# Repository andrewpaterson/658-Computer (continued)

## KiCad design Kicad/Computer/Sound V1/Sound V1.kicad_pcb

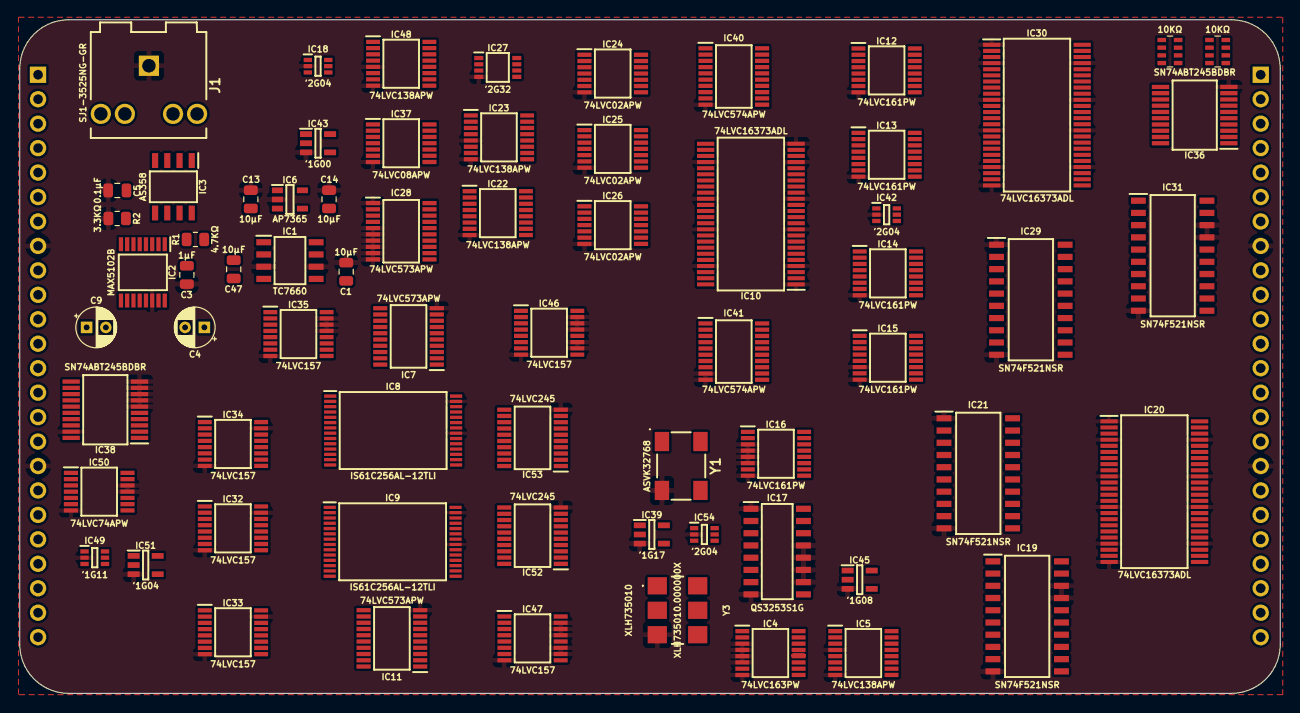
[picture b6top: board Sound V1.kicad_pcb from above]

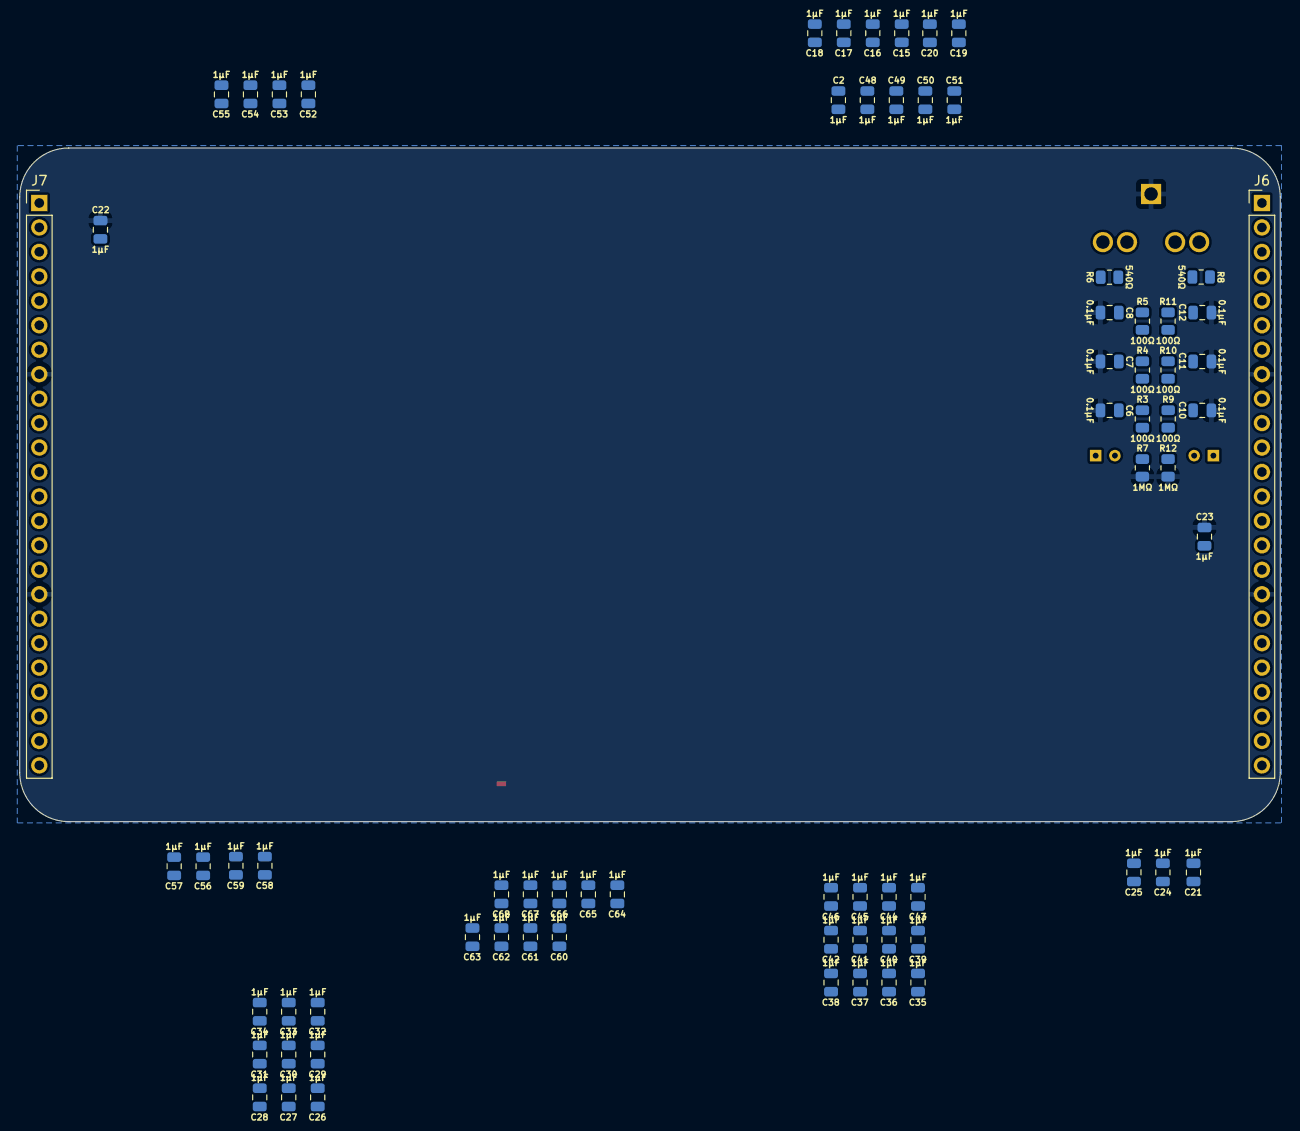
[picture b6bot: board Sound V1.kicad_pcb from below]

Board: 2 copper layers, 130.9 x 70.0 mm, 141 parts (72 on the bottom side), 233 nets, no tracks yet.

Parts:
C1, C13, C14, C47: 10µF; C_0805
C2, C3, C15, C16, C17, C18, C19, C20, C21, C22, C23, C24, C25, C26, C27, C28, C29, C30, C31, C32, C33, C34, C35, C36, C37, C38, C39, C40, C41, C42, C43, C44, C45, C46, C48, C49, C50, C51, C52, C53, C54, C55, C56, C57, C58, C59, C60, C61, C62, C63, C64, C65, C66, C67, C68: 1μF; C_0805
C4, C9: C_Polarized; CP_Radial_D4.0mm_P2.00mm
C5, C6, C7, C8, C10, C11, C12: 0.1μF; C_0805
IC1: TC7660EOA; SOIC127P600X175-8N
IC2: MAX5102BEUE+T; SOP65P640X110-16N
IC3: AS358AMTR-G1; SOIC127P600X175-8N
IC4: 74LVC163PW,118; SOP65P640X110-16N
IC5, IC22, IC23, IC48: 74LVC138APW-Q100J; SOP65P640X110-16N
IC6: AP7365-33WG-7; SOT95P285X130-5N
IC7, IC11, IC28: 74LVC573APW,118; SOP65P640X110-20N
IC8, IC9: IS61C256AL-12TLI; SOP55P1340X120-28N
IC10, IC20, IC30: 74LVC16373ADL,118; SOP64P1025X280-48N
IC12, IC13, IC14, IC15, IC16: 74LVC161PW,112; SOP65P640X110-16N
IC17: QS3253S1G; SOIC127P602X173-16N
IC18, IC42, IC54: 74LVC2G04GW-Q100H; SOP65P210X110-6N
IC19, IC21, IC29, IC31: SN74F521NSR; SOIC127P780X200-20N
IC24, IC25, IC26: 74LVC02APW,118; SOP65P640X110-14N
IC27: 74LVC2G32DP,125; SOP65P400X110-8N
IC32, IC33, IC34, IC35, IC46, IC47: 74LVC157APW,118; SOP65P640X110-16N
IC36, IC38: SN74ABT245BDBR; SOP65P780X200-20N
IC37: 74LVC08APW,112; SOP65P640X110-14N
IC39: 74LVC1G17GV,125; SOT95P275X110-5N
IC40, IC41: 74LVC574APW,118; SOP65P640X110-20N
IC43: 74LVC1G00GV,125; SOT95P275X110-5N
IC45: 74LVC1G08GV,125; SOT95P275X110-5N
IC49: 74LVC1G11GW-Q100H; SOP65P210X110-6N
IC50: 74LVC74APW,118; SOP65P640X110-14N
IC51: 74LVC1G04GV,125; SOT95P275X110-5N
IC52, IC53: 74LVC245AT20; SOP65P640X120-20N
J1: SJ1-3525NG-GR; SJ13525NGGR
J6, J7: Conn_01x24_Pin; PinHeader_1x24_P2.54mm_Vertical
NT1: NetTie; NetTie-2_SMD_Pad0.5mm
R1: 4.7KΩ; R_0805
R2: 3.3KΩ; R_0805
R3, R4, R5, R9, R10, R11: 100Ω; R_0805
R6, R8: 540Ω; R_0805
R7, R12: 1MΩ; R_0805
RN1, RN2: CAY16-103J4LF; CAY16-J4
Y1: ASVK-32.768KHZ-LJT; ASVK32768KHZLJT
Y3: XLH735010.000000X; XLH735010000000X

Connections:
/Sound Clock/3.3V: C2.1, C14.1, C15.1, C16.1, C17.1, C18.1, C19.1, C20.1, C21.1, C24.1, C25.1, C26.1, C27.1, C28.1, C29.1, C30.1, C31.1, C32.1, C33.1, C34.1, C35.1, C36.1, C37.1, C38.1, C39.1, C40.1, C41.1, C42.1, C43.1, C44.1, C48.1, C49.1, C50.1, C51.1, C52.1, C53.1, C56.1, C57.1, C61.1, C62.1, C63.1, C64.1, C65.1, C66.1, C67.1, C68.1, IC4.9 (~PE), IC4.10 (CET), IC4.16 (3V), IC5.16 (3V), IC6.5 (VOUT), IC7.20 (3V), IC10.7 (3V), IC10.18 (3V), IC10.31 (3V), IC10.42 (3V), IC11.20 (3V), IC12.7 (CEP), IC12.10 (CET), IC12.16 (3V), IC13.10 (CET), IC13.16 (3V), IC14.16 (3V), IC15.16 (3V), IC16.7 (CEP), IC16.9 (~PE), IC16.10 (CET), IC16.16 (3V), IC17.15 (~EB), IC18.5 (3V), IC20.7 (3V), IC20.18 (3V), IC20.31 (3V), IC20.42 (3V), IC22.6 (E3), IC22.16 (3V), IC23.16 (3V), IC24.14 (3V), IC25.14 (3V), IC26.9 (3A), IC26.12 (4A), IC26.14 (3V), IC27.8 (VCC), IC28.20 (3V), IC30.7 (3V), IC30.18 (3V), IC30.31 (3V), IC30.42 (3V), IC32.16 (3V), IC33.16 (3V), IC34.16 (3V), IC35.16 (3V), IC37.14 (3V), IC39.5 (3V), IC40.20 (3V), IC41.20 (3V), IC42.5 (3V), IC43.5 (3V), IC45.5 (3V), IC46.6 (2I1), IC46.16 (3V), IC47.6 (2I1), IC47.16 (3V), IC48.16 (3V), IC49.5 (3V), IC50.1 (~1RD), IC50.14 (3V), IC51.5 (3V), IC52.20 (3V), IC53.20 (3V), IC54.5 (3V), RN1.5 (R4), RN1.6 (R3), RN1.7 (R2), RN1.8 (R1), RN2.5 (R4), RN2.6 (R3), RN2.7 (R2), RN2.8 (R1), Y1.4 (3V), Y3.6 (3V)
/Sound Clock/4KHz: IC16.12 (Q2), IC17.3 (I3A)
/Sound Clock/5V: C3.1, C13.1, C22.1, C23.1, C45.1, C46.1, C54.1, C55.1, C58.1, C59.1, C60.1, IC1.8 (V+), IC2.1 (VDD), IC3.8 (VCC), IC6.1 (VIN), IC6.3 (EN), IC8.7 (5V), IC9.7 (5V), IC17.16 (5V), IC19.20 (5V), IC21.20 (5V), IC29.20 (5V), IC31.20 (5V), IC36.20 (5V), IC38.1 (DIR), IC38.20 (5V), J6.3, J7.22, R1.1
/Sound Clock/8KHz: IC16.13 (Q1), IC17.4 (I2A)
/Sound Clock/10MHz: IC4.2 (CP), Y3.4 (OUT)
/Sound Clock/16KHz: IC16.14 (Q0), IC17.5 (I1A)
/Sound Clock/32KHz: IC16.2 (CP), IC17.6 (I0A), Y1.3 (OUTPUT)
/Sound Clock/-5V: C1.2, IC1.5 (VOUT), IC3.4 (GND)
/Sound Clock/A0: IC22.1 (A0), IC23.1 (A0), IC33.2 (1I0), J7.10
/Sound Clock/A1: IC22.2 (A1), IC23.2 (A1), IC33.5 (2I0), J7.11
/Sound Clock/A2: IC22.3 (A2), IC23.3 (A2), IC33.11 (3I0), J7.12
/Sound Clock/A3: IC22.5 (~E2), IC23.6 (E3), IC33.14 (4I0), J7.13
/Sound Clock/A4: IC32.2 (1I0), J7.14
/Sound Clock/A5: IC32.5 (2I0), J7.15
/Sound Clock/A6: IC32.11 (3I0), J7.16
/Sound Clock/A7: IC32.14 (4I0), J7.18
/Sound Clock/A8: IC34.2 (1I0), J7.19
/Sound Clock/A9: IC34.5 (2I0), J7.20
/Sound Clock/A10: IC34.11 (3I0), J7.21
/Sound Clock/A11: IC34.14 (4I0), J7.23
/Sound Clock/A12: IC35.2 (1I0), J7.24
/Sound Clock/A13: IC35.5 (2I0), J6.24
/Sound Clock/A14: IC35.11 (3I0), J6.23
/Sound Clock/A15: IC48.1 (A0), J6.22
/Sound Clock/A16: IC27.6 (2B), IC37.1 (1A), IC43.2 (A), IC48.6 (E3), J6.21
/Sound Clock/A ~OE: IC8.1 (~OE), IC46.4 (1Y)
/Sound Clock/A ~WE: IC8.6 (~WE), IC46.7 (2Y)
/Sound Clock/B ~OE: IC9.1 (~OE), IC47.4 (1Y)
/Sound Clock/B ~WE: IC9.6 (~WE), IC47.7 (2Y)
/Sound Clock/C0: IC12.14 (Q0), IC21.3 (Q0), IC29.3 (Q0), IC33.3 (1I1), IC40.2 (D0)
/Sound Clock/C1: IC12.13 (Q1), IC21.5 (Q1), IC29.5 (Q1), IC33.6 (2I1), IC40.3 (D1)
/Sound Clock/C2: IC12.12 (Q2), IC21.7 (Q2), IC29.7 (Q2), IC33.10 (3I1), IC40.4 (D2)
/Sound Clock/C3: IC12.11 (Q3), IC21.9 (Q3), IC29.9 (Q3), IC33.13 (4I1), IC40.5 (D3)
/Sound Clock/C4: IC13.14 (Q0), IC21.12 (Q4), IC29.12 (Q4), IC32.3 (1I1), IC40.6 (D4)
/Sound Clock/C5: IC13.13 (Q1), IC21.14 (Q5), IC29.14 (Q5), IC32.6 (2I1), IC40.7 (D5)
/Sound Clock/C6: IC13.12 (Q2), IC21.16 (Q6), IC29.16 (Q6), IC32.10 (3I1), IC40.8 (D6)
/Sound Clock/C7: IC13.11 (Q3), IC21.18 (Q7), IC29.18 (Q7), IC32.13 (4I1), IC40.9 (D7)
/Sound Clock/C8: IC14.14 (Q0), IC19.3 (Q0), IC31.3 (Q0), IC34.3 (1I1), IC41.2 (D0)
/Sound Clock/C9: IC14.13 (Q1), IC19.5 (Q1), IC31.5 (Q1), IC34.6 (2I1), IC41.3 (D1)
/Sound Clock/C10: IC14.12 (Q2), IC19.7 (Q2), IC31.7 (Q2), IC34.10 (3I1), IC41.4 (D2)
/Sound Clock/C11: IC14.11 (Q3), IC19.9 (Q3), IC31.9 (Q3), IC34.13 (4I1), IC41.5 (D3)
/Sound Clock/C12: IC15.14 (Q0), IC19.12 (Q4), IC31.12 (Q4), IC35.3 (1I1), IC41.6 (D4)
/Sound Clock/C13: IC15.13 (Q1), IC19.14 (Q5), IC31.14 (Q5), IC35.6 (2I1), IC41.7 (D5)
/Sound Clock/C14: IC15.12 (Q2), IC19.16 (Q6), IC31.16 (Q6), IC35.10 (3I1), IC41.8 (D6)
/Sound Clock/CLK: IC12.2 (CP), IC13.2 (CP), IC14.2 (CP), IC15.2 (CP), IC27.1 (1A), IC39.4 (Y), IC46.3 (1I1), IC47.3 (1I1), IC54.3 (2A)
/Sound Clock/CPU A ~OE: IC37.4 (2A), IC46.2 (1I0), IC48.13 (~Y2)
/Sound Clock/CPU A ~OE·~WE: IC37.6 (2Y), IC53.19 (~OE)
/Sound Clock/CPU A ~WE: IC37.5 (2B), IC46.5 (2I0), IC48.11 (~Y4)
/Sound Clock/CPU B ~OE: IC37.9 (3A), IC47.2 (1I0), IC48.12 (~Y3)
/Sound Clock/CPU B ~OE·~WE: IC37.8 (3Y), IC52.19 (~OE)
/Sound Clock/CPU B ~WE: IC37.10 (3B), IC47.5 (2I0), IC48.10 (~Y5)
/Sound Clock/Clear Interrupt: IC25.8 (3Y), IC51.2 (A)
/Sound Clock/Clear Interrupt ~CS: IC22.9 (~Y6), IC25.9 (3A)
/Sound Clock/Clock Select _{S0}: IC17.14 (S0), IC28.19 (Q0)
/Sound Clock/Clock Select _{S1}: IC17.2 (S1), IC28.18 (Q1)
/Sound Clock/Config ~CS: IC22.4 (~E1), IC23.4 (~E1), IC27.3 (2Y)
/Sound Clock/D0: IC10.26 (2D7), IC10.37 (1D7), IC20.36 (2D0), IC20.47 (1D0), IC28.2 (D0), IC30.36 (2D0), IC30.47 (1D0), IC36.11 (B7), IC40.19 (Q0), IC41.19 (Q0), IC52.18 (B0), IC53.18 (B0), RN2.1 (R1)
/Sound Clock/D0_{IN/OUT}: IC36.9 (A7), J7.1
/Sound Clock/D1: IC10.27 (2D6), IC10.38 (1D6), IC20.35 (2D1), IC20.46 (1D1), IC28.3 (D1), IC30.35 (2D1), IC30.46 (1D1), IC36.12 (B6), IC40.18 (Q1), IC41.18 (Q1), IC52.17 (B1), IC53.17 (B1), RN2.2 (R2)
/Sound Clock/D1_{IN/OUT}: IC36.8 (A6), J7.2
/Sound Clock/D2: IC10.29 (2D5), IC10.40 (1D5), IC20.33 (2D2), IC20.44 (1D2), IC28.4 (D2), IC30.33 (2D2), IC30.44 (1D2), IC36.13 (B5), IC40.17 (Q2), IC41.17 (Q2), IC52.16 (B2), IC53.16 (B2), RN2.3 (R3)
/Sound Clock/D2_{IN/OUT}: IC36.7 (A5), J7.3
/Sound Clock/D3: IC10.30 (2D4), IC10.41 (1D4), IC20.32 (2D3), IC20.43 (1D3), IC30.32 (2D3), IC30.43 (1D3), IC36.14 (B4), IC40.16 (Q3), IC41.16 (Q3), IC52.15 (B3), IC53.15 (B3), RN2.4 (R4)
/Sound Clock/D3_{IN/OUT}: IC36.6 (A4), J7.4
/Sound Clock/D4: IC10.32 (2D3), IC10.43 (1D3), IC20.30 (2D4), IC20.41 (1D4), IC30.30 (2D4), IC30.41 (1D4), IC36.15 (B3), IC40.15 (Q4), IC41.15 (Q4), IC52.14 (B4), IC53.14 (B4), RN1.4 (R4)
/Sound Clock/D4_{IN/OUT}: IC36.5 (A3), J7.5
/Sound Clock/D5: IC10.33 (2D2), IC10.44 (1D2), IC20.29 (2D5), IC20.40 (1D5), IC30.29 (2D5), IC30.40 (1D5), IC36.16 (B2), IC40.14 (Q5), IC41.14 (Q5), IC52.13 (B5), IC53.13 (B5), RN1.3 (R3)
/Sound Clock/D5_{IN/OUT}: IC36.4 (A2), J7.6
/Sound Clock/D6: IC10.35 (2D1), IC10.46 (1D1), IC20.27 (2D6), IC20.38 (1D6), IC30.27 (2D6), IC30.38 (1D6), IC36.17 (B1), IC40.13 (Q6), IC41.13 (Q6), IC52.12 (B6), IC53.12 (B6), RN1.2 (R2)
/Sound Clock/D6_{IN/OUT}: IC36.3 (A1), J7.7
/Sound Clock/D7: IC10.36 (2D0), IC10.47 (1D0), IC20.26 (2D7), IC20.37 (1D7), IC30.26 (2D7), IC30.37 (1D7), IC36.18 (B0), IC40.12 (Q7), IC41.12 (Q7), IC52.11 (B7), IC53.11 (B7), RN1.1 (R1)
/Sound Clock/D7_{IN/OUT}: IC36.2 (A0), J7.9
/Sound Clock/DA0: IC7.2 (D0), IC8.18 (I/O0), IC53.2 (A0)
/Sound Clock/DA1: IC7.3 (D1), IC8.19 (I/O1), IC53.3 (A1)
/Sound Clock/DA2: IC7.4 (D2), IC8.20 (I/O2), IC53.4 (A2)
/Sound Clock/DA3: IC7.5 (D3), IC8.22 (I/O3), IC53.5 (A3)
/Sound Clock/DA4: IC7.6 (D4), IC8.23 (I/O4), IC53.6 (A4)
/Sound Clock/DA5: IC7.7 (D5), IC8.24 (I/O5), IC53.7 (A5)
/Sound Clock/DA6: IC7.8 (D6), IC8.25 (I/O6), IC53.8 (A6)
/Sound Clock/DA7: IC7.9 (D7), IC8.26 (I/O7), IC53.9 (A7)
/Sound Clock/DB0: IC9.18 (I/O0), IC11.2 (D0), IC52.2 (A0)
/Sound Clock/DB1: IC9.19 (I/O1), IC11.3 (D1), IC52.3 (A1)
/Sound Clock/DB2: IC9.20 (I/O2), IC11.4 (D2), IC52.4 (A2)
/Sound Clock/DB3: IC9.22 (I/O3), IC11.5 (D3), IC52.5 (A3)
/Sound Clock/DB4: IC9.23 (I/O4), IC11.6 (D4), IC52.6 (A4)
/Sound Clock/DB5: IC9.24 (I/O5), IC11.7 (D5), IC52.7 (A5)
/Sound Clock/DB6: IC9.25 (I/O6), IC11.8 (D6), IC52.8 (A6)
/Sound Clock/DB7: IC9.26 (I/O7), IC11.9 (D7), IC52.9 (A7)
/Sound Clock/Device CS: IC18.6 (1Y), IC37.2 (1B), IC43.1 (B)
/Sound Clock/Device ~CS: IC18.1 (1A), IC27.5 (2A), IC36.19 (~OE), IC38.15 (B3), IC48.4 (~E1)
/Sound Clock/Device ~CS _{IN}: IC38.5 (A3), J6.11
/Sound Clock/EC0: IC20.2 (1Q0), IC21.2 (P0)
/Sound Clock/EC1: IC20.3 (1Q1), IC21.4 (P1)
/Sound Clock/EC2: IC20.5 (1Q2), IC21.6 (P2)
/Sound Clock/EC3: IC20.6 (1Q3), IC21.8 (P3)
/Sound Clock/EC4: IC20.8 (1Q4), IC21.11 (P4)
/Sound Clock/EC5: IC20.9 (1Q5), IC21.13 (P5)
/Sound Clock/EC6: IC20.11 (1Q6), IC21.15 (P6)
/Sound Clock/EC7: IC20.12 (1Q7), IC21.17 (P7)
/Sound Clock/EC8: IC19.2 (P0), IC20.13 (2Q0)
/Sound Clock/EC9: IC19.4 (P1), IC20.14 (2Q1)
/Sound Clock/EC10: IC19.6 (P2), IC20.16 (2Q2)
/Sound Clock/EC11: IC19.8 (P3), IC20.17 (2Q3)
/Sound Clock/EC12: IC19.11 (P4), IC20.19 (2Q4)
/Sound Clock/EC13: IC19.13 (P5), IC20.20 (2Q5)
/Sound Clock/EC14: IC19.15 (P6), IC20.22 (2Q6)
/Sound Clock/Enable: IC12.1 (~MR), IC13.1 (~MR), IC14.1 (~MR), IC15.1 (~MR), IC37.12 (4A), IC50.9 (2Q)
/Sound Clock/GND: C1.1, C2.2, C3.2, C5.1, C6.1, C7.1, C8.1, C10.1, C11.1, C12.1, C13.2, C14.2, C15.2, C16.2, C17.2, C18.2, C19.2, C20.2, C21.2, C22.2, C23.2, C24.2, C25.2, C26.2, C27.2, C28.2, C29.2, C30.2, C31.2, C32.2, C33.2, C34.2, C35.2, C36.2, C37.2, C38.2, C39.2, C40.2, C41.2, C42.2, C43.2, C44.2, C45.2, C46.2, C48.2, C49.2, C50.2, C51.2, C52.2, C53.2, C54.2, C55.2, C56.2, C57.2, C58.2, C59.2, C60.2, C61.2, C62.2, C63.2, C64.2, C65.2, C66.2, C67.2, C68.2, IC1.3 (GND), IC1.6 (LV), IC2.14 (GND), IC4.3 (D0), IC4.4 (D1), IC4.5 (D2), IC4.6 (D3), IC4.8 (GND), IC5.4 (~E1), IC5.8 (GND), IC6.2 (GND), IC7.10 (GND), IC8.21 (GND), IC8.27 (~CE), IC9.21 (GND), IC9.27 (~CE), IC10.1 (1~OE), IC10.4 (GND), IC10.10 (GND), IC10.15 (GND), IC10.21 (GND), IC10.24 (2~OE), IC10.28 (GND), IC10.34 (GND), IC10.39 (GND), IC10.45 (GND), IC11.10 (GND), IC12.8 (GND), IC13.8 (GND), IC14.8 (GND), IC15.6 (D3), IC15.8 (GND), IC16.3 (D0), IC16.4 (D1), IC16.5 (D2), IC16.6 (D3), IC16.8 (GND), IC17.1 (~EA), IC17.8 (GND), IC17.10 (I0B), IC17.11 (I1B), IC17.12 (I2B), IC17.13 (I3B), IC18.2 (GND), IC19.10 (GND), IC19.17 (P7), IC19.18 (Q7), IC20.1 (1~OE), IC20.4 (GND), IC20.10 (GND), IC20.15 (GND), IC20.21 (GND), IC20.24 (2~OE), IC20.28 (GND), IC20.34 (GND), IC20.39 (GND), IC20.45 (GND), IC21.1 (~OE), IC21.10 (GND), IC22.8 (GND), IC23.5 (~E2), IC23.8 (GND), IC24.7 (GND), IC25.7 (GND), IC26.7 (GND), IC27.4 (GND), IC28.1 (~OE), IC28.5 (D3), IC28.6 (D4), IC28.7 (D5), IC28.8 (D6), IC28.9 (D7), IC28.10 (GND), IC29.1 (~OE), IC29.10 (GND), IC30.1 (1~OE), IC30.4 (GND), IC30.10 (GND), IC30.15 (GND), IC30.21 (GND), IC30.24 (2~OE), IC30.28 (GND), IC30.34 (GND), IC30.39 (GND), IC30.45 (GND), IC31.10 (GND), IC31.17 (P7), IC31.18 (Q7), IC32.8 (GND), IC32.15 (~E), IC33.8 (GND), IC33.15 (~E), IC34.8 (GND), IC34.15 (~E), IC35.8 (GND), IC35.13 (4I1), IC35.14 (4I0), IC35.15 (~E), IC36.10 (GND), IC37.7 (GND), IC38.6 (A4), IC38.7 (A5), IC38.8 (A6), IC38.9 (A7), IC38.10 (GND), IC38.19 (~OE), IC39.3 (GND), IC40.10 (GND), IC41.9 (D7), IC41.10 (GND), IC42.2 (GND), IC43.3 (GND), IC45.3 (GND), IC46.8 (GND), IC46.10 (3I1), IC46.11 (3I0), IC46.13 (4I1), IC46.14 (4I0), IC46.15 (~E), IC47.8 (GND), IC47.10 (3I1), IC47.11 (3I0), IC47.13 (4I1), IC47.14 (4I0), IC47.15 (~E), IC48.5 (~E2), IC48.8 (GND), IC49.2 (GND), IC50.7 (GND), IC50.11 (2CP), IC50.12 (2D), IC51.3 (GND), IC52.10 (GND), IC53.10 (GND), IC54.2 (GND), J1.1 (GND), J6.8, J6.17, J7.8, J7.17, R2.1, R7.1, R12.1, Y1.2 (GND), Y3.3 (GND)
/Sound Clock/IC0: IC29.2 (P0), IC30.2 (1Q0)
/Sound Clock/IC1: IC29.4 (P1), IC30.3 (1Q1)
/Sound Clock/IC2: IC29.6 (P2), IC30.5 (1Q2)
/Sound Clock/IC3: IC29.8 (P3), IC30.6 (1Q3)
/Sound Clock/IC4: IC29.11 (P4), IC30.8 (1Q4)
/Sound Clock/IC5: IC29.13 (P5), IC30.9 (1Q5)
/Sound Clock/IC6: IC29.15 (P6), IC30.11 (1Q6)
/Sound Clock/IC7: IC29.17 (P7), IC30.12 (1Q7)
/Sound Clock/IC8: IC30.13 (2Q0), IC31.2 (P0)
/Sound Clock/IC9: IC30.14 (2Q1), IC31.4 (P1)
/Sound Clock/IC10: IC30.16 (2Q2), IC31.6 (P2)
/Sound Clock/IC11: IC30.17 (2Q3), IC31.8 (P3)
/Sound Clock/IC12: IC30.19 (2Q4), IC31.11 (P4)
/Sound Clock/IC13: IC30.20 (2Q5), IC31.13 (P5)
/Sound Clock/IC14: IC30.22 (2Q6), IC31.15 (P6)
/Sound Clock/Interrupt Enable: IC37.11 (4Y), IC49.3 (B)
/Sound Clock/LC0: IC10.23 (2Q7), IC12.3 (D0)
/Sound Clock/LC1: IC10.22 (2Q6), IC12.4 (D1)
/Sound Clock/LC2: IC10.20 (2Q5), IC12.5 (D2)
/Sound Clock/LC3: IC10.19 (2Q4), IC12.6 (D3)
/Sound Clock/LC4: IC10.17 (2Q3), IC13.3 (D0)
/Sound Clock/LC5: IC10.16 (2Q2), IC13.4 (D1)
/Sound Clock/LC6: IC10.14 (2Q1), IC13.5 (D2)
/Sound Clock/LC7: IC10.13 (2Q0), IC13.6 (D3)
/Sound Clock/LC8: IC10.12 (1Q7), IC14.3 (D0)
/Sound Clock/LC9: IC10.11 (1Q6), IC14.4 (D1)
/Sound Clock/LC10: IC10.9 (1Q5), IC14.5 (D2)
/Sound Clock/LC11: IC10.8 (1Q4), IC14.6 (D3)
/Sound Clock/LC12: IC10.6 (1Q3), IC15.3 (D0)
/Sound Clock/LC13: IC10.5 (1Q2), IC15.4 (D1)
/Sound Clock/LC14: IC10.3 (1Q1), IC15.5 (D2)
/Sound Clock/Line Out Left: J1.3 (L), R6.2
/Sound Clock/Line Out Right: J1.2 (R), R8.2
/Sound Clock/M0: IC8.17 (A0), IC9.17 (A0), IC33.4 (1Y)
/Sound Clock/M1: IC8.16 (A1), IC9.16 (A1), IC33.7 (2Y)
/Sound Clock/M2: IC8.15 (A2), IC9.15 (A2), IC33.9 (3Y)
/Sound Clock/M3: IC8.14 (A3), IC9.14 (A3), IC33.12 (4Y)
/Sound Clock/M4: IC8.13 (A4), IC9.13 (A4), IC32.4 (1Y)
/Sound Clock/M5: IC8.12 (A5), IC9.12 (A5), IC32.7 (2Y)
/Sound Clock/M6: IC8.11 (A6), IC9.11 (A6), IC32.9 (3Y)
/Sound Clock/M7: IC8.10 (A7), IC9.10 (A7), IC32.12 (4Y)
/Sound Clock/M8: IC8.4 (A8), IC9.4 (A8), IC34.4 (1Y)
/Sound Clock/M9: IC8.3 (A9), IC9.3 (A9), IC34.7 (2Y)
/Sound Clock/M10: IC8.28 (A10), IC9.28 (A10), IC34.9 (3Y)
/Sound Clock/M11: IC8.2 (A11), IC9.2 (A11), IC34.12 (4Y)
/Sound Clock/M12: IC8.9 (A12), IC9.9 (A12), IC35.4 (1Y)
/Sound Clock/M13: IC8.5 (A13), IC9.5 (A13), IC35.7 (2Y)
/Sound Clock/M14: IC8.8 (A14), IC9.8 (A14), IC35.9 (3Y)
/Sound Clock/MAX0: IC2.9 (D3), IC7.19 (Q0), IC11.19 (Q0)
/Sound Clock/MAX1: IC2.10 (D2), IC7.18 (Q1), IC11.18 (Q1)
/Sound Clock/MAX2: IC2.11 (D1), IC7.17 (Q2), IC11.17 (Q2)
/Sound Clock/MAX3: IC2.12 (D0), IC7.16 (Q3), IC11.16 (Q3)
/Sound Clock/MAX4: IC2.8 (D4), IC7.15 (Q4), IC11.15 (Q4)
/Sound Clock/MAX5: IC2.7 (D5), IC7.14 (Q5), IC11.14 (Q5)
/Sound Clock/MAX6: IC2.6 (D6), IC7.13 (Q6), IC11.13 (Q6)
/Sound Clock/MAX7: IC2.5 (D7), IC7.12 (Q7), IC11.12 (Q7)
/Sound Clock/MAX_{A0}: IC2.13 (A0), NT1.2
/Sound Clock/MAX_{~WR}: IC2.4 (~WR), IC45.4 (Y)
/Sound Clock/Q0: IC4.14 (Q0), IC5.1 (A0)
/Sound Clock/Q1: IC4.13 (Q1), IC5.2 (A1)
/Sound Clock/Q2: IC4.12 (Q2), IC5.3 (A2), NT1.1
/Sound Clock/Q3: IC4.11 (Q3), IC5.5 (~E2), IC54.1 (1A)
/Sound Clock/Read Address High: IC26.6 (2Y), IC42.3 (2A)
/Sound Clock/Read Address High ~CS: IC23.14 (~Y1), IC26.5 (2B)
/Sound Clock/Read Address Low: IC26.3 (1Y), IC40.11 (CP), IC41.11 (CP), IC42.1 (1A)
/Sound Clock/Read Address Low ~CS: IC23.15 (~Y0), IC26.2 (1B)
/Sound Clock/Reset Disable ~CS: IC23.7 (~Y7), IC50.10 (~2SD)
/Sound Clock/Sound Address: IC7.11 (LE), IC11.11 (LE), IC18.4 (2Y)
/Sound Clock/TC_{0..3}: IC12.15 (TC), IC13.7 (CEP), IC14.7 (CEP), IC15.7 (CEP)
/Sound Clock/TC_{4..7}: IC13.15 (TC), IC14.10 (CET)
/Sound Clock/TC_{8..11}: IC14.15 (TC), IC15.10 (CET)
/Sound Clock/Write End Address High: IC20.25 (2LE), IC24.11 (4Y)
/Sound Clock/Write End Address High ~CS: IC22.12 (~Y3), IC24.12 (4A)
/Sound Clock/Write End Address Low: IC20.48 (1LE), IC24.8 (3Y)
/Sound Clock/Write End Address Low ~CS: IC22.13 (~Y2), IC24.9 (3A)
/Sound Clock/Write Flags: IC25.11 (4Y), IC28.11 (LE)
/Sound Clock/Write Flags ~CS: IC22.7 (~Y7), IC25.12 (4A)
/Sound Clock/Write Interrupt Address High: IC25.6 (2Y), IC30.25 (2LE)
/Sound Clock/Write Interrupt Address High ~CS: IC22.10 (~Y5), IC25.4 (2A)
/Sound Clock/Write Interrupt Address Low: IC25.3 (1Y), IC30.48 (1LE)
/Sound Clock/Write Interrupt Address Low ~CS: IC22.11 (~Y4), IC25.1 (1A)
/Sound Clock/Write Start Address High: IC10.25 (2LE), IC24.6 (2Y)
/Sound Clock/Write Start Address High ~CS: IC22.14 (~Y1), IC24.4 (2A)
/Sound Clock/Write Start Address Low: IC10.48 (1LE), IC24.3 (1Y)
/Sound Clock/Write Start Address Low ~CS: IC22.15 (~Y0), IC24.1 (1A)
/Sound Clock/~CLK: IC4.1 (~MR), IC5.6 (E3), IC50.3 (1CP), IC54.4 (2Y)
/Sound Clock/~CPU Address: IC32.1 (S), IC33.1 (S), IC34.1 (S), IC35.1 (S), IC43.4 (Y), IC46.1 (S), IC47.1 (S)
/Sound Clock/~Clear Interrupt: IC49.6 (C), IC51.4 (Y)
/Sound Clock/~Enable _{OUT}: IC2.3 (SHDN), IC50.8 (~2Q), J6.19
/Sound Clock/~End _{CMP}: IC12.9 (~PE), IC13.9 (~PE), IC14.9 (~PE), IC15.9 (~PE), IC19.19 (~P=Q)
/Sound Clock/~Interrupt _{CMP}: IC31.19 (~P=Q), IC50.2 (1D)
/Sound Clock/~Interrupt _{OUT}: IC50.5 (1Q), J6.18
/Sound Clock/~Q3: IC4.7 (CEP), IC54.6 (1Y)
/Sound Clock/~RD: IC26.1 (1A), IC26.4 (2A), IC36.1 (DIR), IC38.16 (B2), IC48.3 (A2)
/Sound Clock/~RD_{IN}: IC38.4 (A2), J6.13
/Sound Clock/~Read Address High: IC41.1 (~OE), IC42.4 (2Y)
/Sound Clock/~Read Address Low: IC40.1 (~OE), IC42.6 (1Y), J6.10
/Sound Clock/~Reset: IC16.1 (~MR), IC38.18 (B0), IC49.1 (A), IC50.13 (~2RD)
/Sound Clock/~Reset _{IN}: IC38.2 (A0), J6.1
/Sound Clock/~Sound Address: IC18.3 (2A), IC27.7 (1Y)
/Sound Clock/~WD: IC24.2 (1B), IC24.5 (2B), IC24.10 (3B), IC24.13 (4B), IC25.2 (1B), IC25.5 (2B), IC25.10 (3B), IC25.13 (4B), IC26.10 (3B), IC26.13 (4B), IC38.17 (B1), IC48.2 (A1), IC52.1 (DIR), IC53.1 (DIR)
/Sound Clock/~WD_{IN}: IC38.3 (A1), J6.12
/Sound Clock/~WR_{A}: IC5.14 (~Y1), IC7.1 (~OE), IC45.2 (A)
/Sound Clock/~WR_{B}: IC5.12 (~Y3), IC11.1 (~OE), IC45.1 (B)
unnamed: C4.2, R3.1, R7.2
unnamed: C6.2, R3.2, R4.1
unnamed: C7.2, R4.2, R5.1
unnamed: C9.2, R9.1, R12.2
unnamed: C10.2, R9.2, R10.1
unnamed: C11.2, R10.2, R11.1
unnamed: C47.1, IC1.2 (CAP+)
unnamed: C47.2, IC1.4 (CAP-)
unnamed: C4.1, IC2.16 (OUTA)
unnamed: C9.1, IC2.15 (OUTB)
unnamed: C5.2, IC2.2 (REF), R1.2, R2.2
unnamed: C8.2, IC3.3 (IN_1+), R5.2
unnamed: IC3.1 (OUT_1), IC3.2 (IN_1-), R6.1
unnamed: C12.2, IC3.5 (IN_2+), R11.2
unnamed: IC3.6 (IN_2-), IC3.7 (OUT_2), R8.1
unnamed: IC17.7 (YA), IC39.2 (A)
unnamed: IC19.1 (~OE), IC21.19 (~P=Q)
unnamed: IC27.2 (1B), IC37.3 (1Y)
unnamed: IC28.17 (Q2), IC37.13 (4B)
unnamed: IC29.19 (~P=Q), IC31.1 (~OE)
unnamed: IC49.4 (Y), IC50.4 (~1SD)

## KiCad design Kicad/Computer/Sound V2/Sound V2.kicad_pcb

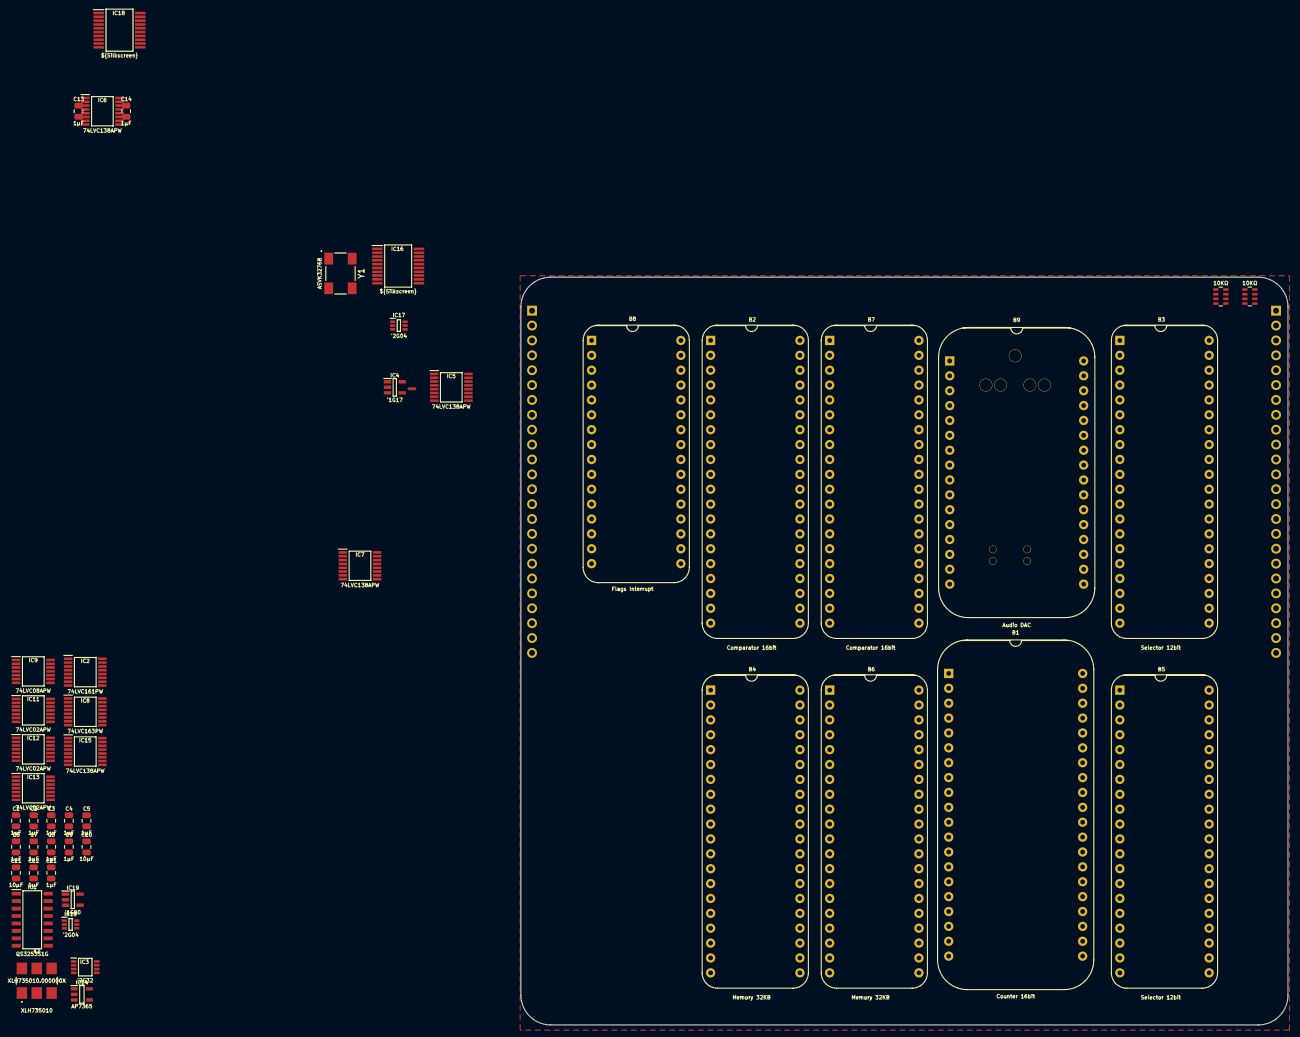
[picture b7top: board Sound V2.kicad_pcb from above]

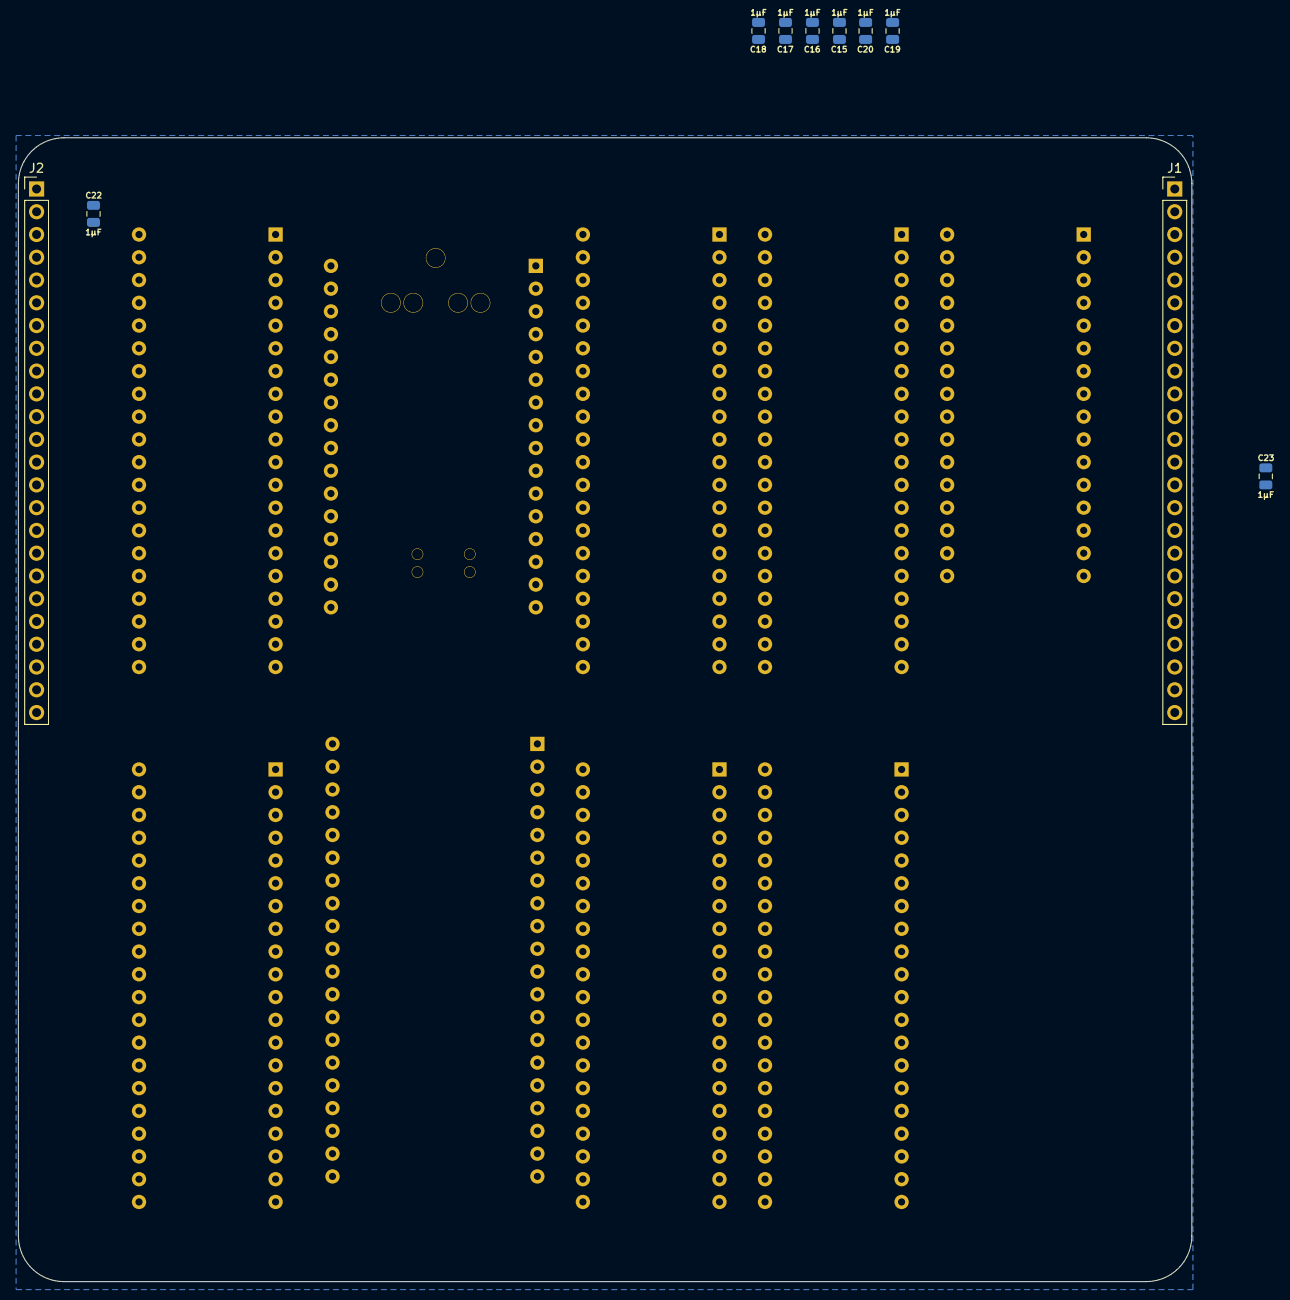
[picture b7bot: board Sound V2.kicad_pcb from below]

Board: 2 copper layers, 130.9 x 127.6 mm, 58 parts (10 on the bottom side), 143 nets, no tracks yet.

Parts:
B1: Count and Start Address; HCP65_Counter_16bit_DIO
B2: Interrupt Address; HCP65_Comparator_16bit
B3: Memory Select (M0..M11); HCP65_Selector_12bit
B4: Memory A; HCP65_Memory_32KB_With_Latch
B5: Memory Select (M12..M14,S,E); HCP65_Selector_12bit
B6: Memory B; HCP65_Memory_32KB_With_Latch
B7: End Address; HCP65_Comparator_16bit
B8: Flags, Interrupt and Enable; HCP65_Flags_Interrupt
B9: Audio DAC; HCP65_Audio_DAC
C1, C2, C3, C4, C5, C6, C7, C8, C9, C12, C13, C14, C15, C16, C17, C18, C19, C20, C21, C22, C23: 1μF; C_0805
C10, C11: 10µF; C_0805
IC1: QS3253S1G; SOIC127P602X173-16N
IC2: 74LVC161PW,112; SOP65P640X110-16N
IC3: 74LVC2G32DP,125; SOP65P400X110-8N
IC4: 74LVC1G17GV,125; SOT95P275X110-5N
IC5, IC6, IC7, IC15: 74LVC138APW-Q100J; SOP65P640X110-16N
IC8: 74LVC163PW,118; SOP65P640X110-16N
IC9: 74LVC08APW,112; SOP65P640X110-14N
IC10, IC17: 74LVC2G04GW-Q100H; SOP65P210X110-6N
IC11, IC12, IC13: 74LVC02APW,118; SOP65P640X110-14N
IC14: AP7365-33WG-7; SOT95P285X130-5N
IC16, IC18: SN74ABT245BDBR; SOP65P780X200-20N
IC19: 74LVC1G00GV,125; SOT95P275X110-5N
J1, J2: Conn_01x24_Pin; PinHeader_1x24_P2.54mm_Vertical
NT1: NetTie; NetTie-2_SMD_Pad0.5mm
RN1, RN2: CAY16-103J4LF; CAY16-J4
Y1: ASVK-32.768KHZ-LJT; ASVK32768KHZLJT
Y2: XLH735010.000000X; XLH735010000000X

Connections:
/3.3V: B1.17 (CE), B5.16 (B10), B5.21 (B6), C1.1, C2.1, C3.1, C4.1, C5.1, C6.1, C7.1, C8.1, C11.1, C12.1, C13.1, C14.1, C15.1, C16.1, C17.1, C18.1, C19.1, C20.1, C21.1, IC1.15 (~EB), IC2.7 (CEP), IC2.9 (~PE), IC2.10 (CET), IC2.16 (3V), IC3.8 (VCC), IC4.5 (3V), IC5.6 (E3), IC5.16 (3V), IC6.16 (3V), IC7.16 (3V), IC8.9 (~PE), IC8.10 (CET), IC8.16 (3V), IC9.14 (3V), IC10.5 (3V), IC11.14 (3V), IC12.14 (3V), IC13.9 (3A), IC13.12 (4A), IC13.14 (3V), IC14.5 (VOUT), IC15.16 (3V), IC17.5 (3V), IC19.5 (3V), RN1.5 (R4), RN1.6 (R3), RN1.7 (R2), RN1.8 (R1), RN2.5 (R4), RN2.6 (R3), RN2.7 (R2), RN2.8 (R1), Y1.4 (3V), Y2.6 (3V)
/4KHz: IC1.3 (I3A), IC2.12 (Q2)
/5V: B1.3 (5V), B1.23 (5V), B2.3 (5V), B2.23 (5V), B3.20 (5V), B4.20 (5V), B5.20 (5V), B6.20 (5V), B7.3 (5V), B7.23 (5V), B8.16 (5V), C9.1, C10.1, C22.1, C23.1, IC1.16 (5V), IC14.1 (VIN), IC14.3 (EN), IC16.20 (5V), IC18.1 (DIR), IC18.20 (5V), J1.3, J2.22
/8KHz: IC1.4 (I2A), IC2.13 (Q1)
/10MHz: IC8.2 (CP), Y2.4 (OUT)
/16KHz: IC1.5 (I1A), IC2.14 (Q0)
/32KHz: IC1.6 (I0A), IC2.2 (CP), Y1.3 (OUTPUT)
/A0: B3.14 (A0), IC5.1 (A0), IC6.1 (A0), J2.10
/A1: B3.13 (A1), IC5.2 (A1), IC6.2 (A1), J2.11
/A2: B3.12 (A2), IC5.3 (A2), IC6.3 (A2), J2.12
/A3: B3.11 (A3), IC5.5 (~E2), IC6.6 (E3), J2.13
/A4: B3.10 (A4), J2.14
/A5: B3.9 (A5), J2.15
/A6: B3.8 (A6), J2.16
/A7: B3.7 (A7), J2.18
/A8: B3.6 (A8), J2.19
/A9: B3.5 (A9), J2.20
/A10: B3.4 (A10), J2.21
/A11: B3.3 (A11), J2.23
/A12: B5.14 (A0), J2.24
/A13: B5.13 (A1), J1.24
/A14: B5.12 (A2), J1.23
/A15: IC15.1 (A0), J1.22
/A16: IC3.6 (2B), IC9.12 (4A), IC15.6 (E3), IC19.2 (A), J1.21
/A ~OE: B4.3 (M~OE), B5.39 (Q11)
/A ~WE: B4.4 (M~WE), B5.38 (Q10)
/B ~OE: B5.35 (Q7), B6.3 (M~OE)
/B ~WE: B5.34 (Q6), B6.4 (M~WE)
/C0: B1.21 (C0), B2.21 (C0), B3.27 (B0), B7.21 (C0)
/C1: B1.22 (C1), B2.22 (C1), B3.26 (B1), B7.22 (C1)
/C2: B1.24 (C2), B2.24 (C2), B3.25 (B2), B7.24 (C2)
/C3: B1.25 (C3), B2.25 (C3), B3.24 (B3), B7.25 (C3)
/C4: B1.27 (C4), B2.27 (C4), B3.23 (B4), B7.27 (C4)
/C5: B1.28 (C5), B2.28 (C5), B3.22 (B5), B7.28 (C5)
/C6: B1.29 (C6), B2.29 (C6), B3.21 (B6), B7.29 (C6)
/C7: B1.30 (C7), B2.30 (C7), B3.19 (B7), B7.30 (C7)
/C8: B1.31 (C8), B2.31 (C8), B3.18 (B8), B7.31 (C8)
/C9: B1.32 (C9), B2.32 (C9), B3.17 (B9), B7.32 (C9)
/C10: B1.33 (C10), B2.33 (C10), B3.16 (B10), B7.33 (C10)
/C11: B1.35 (C11), B2.35 (C11), B3.15 (B11), B7.35 (C11)
/C12: B1.36 (C12), B2.36 (C12), B5.27 (B0), B7.36 (C12)
/C13: B1.37 (C13), B2.37 (C13), B5.26 (B1), B7.37 (C13)
/C14: B1.38 (C14), B2.38 (C14), B5.25 (B2), B7.38 (C14)
/CLK: B1.4 (CP), B5.15 (B11), B5.19 (B7), IC3.1 (1A), IC4.4 (Y), IC10.3 (2A)
/CPU A ~OE: B5.3 (A11), IC9.1 (1A), IC15.13 (~Y2)
/CPU A ~OE·~WE: B4.1 (T~OE), IC9.3 (1Y)
/CPU A ~WE: B5.4 (A10), IC9.2 (1B), IC15.11 (~Y4)
/CPU B ~OE: B5.7 (A7), IC9.4 (2A), IC15.12 (~Y3)
/CPU B ~OE·~WE: B6.1 (T~OE), IC9.6 (2Y)
/CPU B ~WE: B5.8 (A6), IC9.5 (2B), IC15.10 (~Y5)
/Clear Interrupt: B8.4 (Clear_Interrupt), IC12.8 (3Y)
/Clear Interrupt ~CS: IC5.9 (~Y6), IC12.9 (3A)
/Clock Select _{S0}: B8.18 (F0), IC1.14 (S0)
/Clock Select _{S1}: B8.19 (F1), IC1.2 (S1)
/Config ~CS: IC3.3 (2Y), IC5.4 (~E1), IC6.4 (~E1)
/D0: B1.16 (D0), B2.16 (D0), B4.32 (D0), B6.32 (D0), B7.16 (D0), B8.15 (D0), IC16.11 (B7), RN2.1 (R1)
/D0_{IN/OUT}: IC16.9 (A7), J2.1
/D1: B1.14 (D1), B2.14 (D1), B4.33 (D1), B6.33 (D1), B7.14 (D1), B8.14 (D1), IC16.12 (B6), RN2.2 (R2)
/D1_{IN/OUT}: IC16.8 (A6), J2.2
/D2: B1.13 (D2), B2.13 (D2), B4.34 (D2), B6.34 (D2), B7.13 (D2), B8.13 (D2), IC16.13 (B5), RN2.3 (R3)
/D2_{IN/OUT}: IC16.7 (A5), J2.3
/D3: B1.12 (D3), B2.12 (D3), B4.35 (D3), B6.35 (D3), B7.12 (D3), B8.12 (D3), IC16.14 (B4), RN2.4 (R4)
/D3_{IN/OUT}: IC16.6 (A4), J2.4
/D4: B1.11 (D4), B2.11 (D4), B4.36 (D4), B6.36 (D4), B7.11 (D4), B8.11 (D4), IC16.15 (B3), RN1.4 (R4)
/D4_{IN/OUT}: IC16.5 (A3), J2.5
/D5: B1.10 (D5), B2.10 (D5), B4.37 (D5), B6.37 (D5), B7.10 (D5), B8.10 (D5), IC16.16 (B2), RN1.3 (R3)
/D5_{IN/OUT}: IC16.4 (A2), J2.6
/D6: B1.9 (D6), B2.9 (D6), B4.38 (D6), B6.38 (D6), B7.9 (D6), B8.9 (D6), IC16.17 (B1), RN1.2 (R2)
/D6_{IN/OUT}: IC16.3 (A1), J2.7
/D7: B1.8 (D7), B2.8 (D7), B4.39 (D7), B6.39 (D7), B7.8 (D7), B8.8 (D7), IC16.18 (B0), RN1.1 (R1)
/D7_{IN/OUT}: IC16.2 (A0), J2.9
/Device CS: IC9.13 (4B), IC17.6 (1Y), IC19.1 (B)
/Device ~CS: IC3.5 (2A), IC15.4 (~E1), IC16.19 (~OE), IC17.1 (1A), IC18.15 (B3)
/Device ~CS _{IN}: IC18.5 (A3), J1.11
/Enable: B1.6 (~MR), B8.27 (E)
/GND: B1.7 (GND), B1.15 (GND), B1.26 (GND), B1.34 (GND), B2.6 (~OE), B2.7 (GND), B2.15 (GND), B2.26 (GND), B2.34 (GND), B2.39 (C15), B3.1 (E), B3.40 (GND), B4.21 (GND), B4.40 (GND), B5.1 (E), B5.5 (A9), B5.6 (A8), B5.9 (A5), B5.10 (A4), B5.11 (A3), B5.17 (B9), B5.18 (B8), B5.22 (B5), B5.23 (B4), B5.24 (B3), B5.40 (GND), B6.21 (GND), B6.40 (GND), B7.6 (~OE), B7.7 (GND), B7.15 (GND), B7.26 (GND), B7.34 (GND), B7.39 (C15), B8.32 (GND), C1.2, C2.2, C3.2, C4.2, C5.2, C6.2, C7.2, C8.2, C9.2, C10.2, C11.2, C12.2, C13.2, C14.2, C15.2, C16.2, C17.2, C18.2, C19.2, C20.2, C21.2, C22.2, C23.2, IC1.1 (~EA), IC1.8 (GND), IC1.10 (I0B), IC1.11 (I1B), IC1.12 (I2B), IC1.13 (I3B), IC2.3 (D0), IC2.4 (D1), IC2.5 (D2), IC2.6 (D3), IC2.8 (GND), IC3.4 (GND), IC4.3 (GND), IC5.8 (GND), IC6.5 (~E2), IC6.8 (GND), IC7.4 (~E1), IC7.8 (GND), IC8.3 (D0), IC8.4 (D1), IC8.5 (D2), IC8.6 (D3), IC8.8 (GND), IC9.7 (GND), IC10.2 (GND), IC11.7 (GND), IC12.7 (GND), IC13.7 (GND), IC14.2 (GND), IC15.5 (~E2), IC15.8 (GND), IC16.10 (GND), IC17.2 (GND), IC18.6 (A4), IC18.7 (A5), IC18.8 (A6), IC18.9 (A7), IC18.10 (GND), IC18.19 (~OE), IC19.3 (GND), J1.8, J1.17, J2.8, J2.17, Y1.2 (GND), Y2.3 (GND)
/M0: B3.28 (Q0), B4.19 (M0), B6.19 (M0)
/M1: B3.29 (Q1), B4.18 (M1), B6.18 (M1)
/M2: B3.30 (Q2), B4.17 (M2), B6.17 (M2)
/M3: B3.31 (Q3), B4.16 (M3), B6.16 (M3)
/M4: B3.32 (Q4), B4.15 (M4), B6.15 (M4)
/M5: B3.33 (Q5), B4.14 (M5), B6.14 (M5)
/M6: B3.34 (Q6), B4.13 (M6), B6.13 (M6)
/M7: B3.35 (Q7), B4.12 (M7), B6.12 (M7)
/M8: B3.36 (Q8), B4.11 (M8), B6.11 (M8)
/M9: B3.37 (Q9), B4.10 (M9), B6.10 (M9)
/M10: B3.38 (Q10), B4.9 (M10), B6.9 (M10)
/M11: B3.39 (Q11), B4.8 (M11), B6.8 (M11)
/M12: B4.7 (M12), B5.29 (Q1), B6.7 (M12)
/M13: B4.6 (M13), B5.30 (Q2), B6.6 (M13)
/M14: B4.5 (M14), B5.31 (Q3), B6.5 (M14)
/MAX0: B4.24 (LQ0), B6.24 (LQ0)
/MAX1: B4.25 (LQ1), B6.25 (LQ1), B9.15 (D0)
/MAX2: B4.26 (LQ2), B6.26 (LQ2), B9.14 (D1)
/MAX3: B4.27 (LQ3), B6.27 (LQ3), B9.13 (D2)
/MAX4: B4.28 (LQ4), B6.28 (LQ4), B9.12 (D3)
/MAX5: B4.29 (LQ5), B6.29 (LQ5), B9.11 (D4)
/MAX6: B4.30 (LQ6), B6.30 (LQ6), B9.10 (D5)
/MAX7: B4.31 (LQ7), B6.31 (LQ7), B9.9 (D6)
/MAX_{A0}: B9.6 (A0), NT1.2
/MAX_{~WR}: B9.7 (~WR), IC9.8 (3Y)
/Q0: IC7.1 (A0), IC8.14 (Q0)
/Q1: IC7.2 (A1), IC8.13 (Q1)
/Q2: IC7.3 (A2), IC8.12 (Q2), NT1.1
/Q3: IC7.5 (~E2), IC8.11 (Q3), IC10.1 (1A)
/Read Address High: B1.1 (RAH), IC13.6 (2Y)
/Read Address High ~CS: IC6.14 (~Y1), IC13.5 (2B)
/Read Address Low: B1.2 (RAL), IC13.3 (1Y)
/Read Address Low ~CS: IC6.15 (~Y0), IC13.2 (1B)
/Reset Disable ~CS: B8.6 (~Set_Enable), IC6.7 (~Y7)
/Sound Address: B4.22 (LLE), B6.22 (LLE), IC17.4 (2Y)
/Write End Address High: B7.19 (WCAH), IC11.11 (4Y)
/Write End Address High ~CS: IC5.12 (~Y3), IC11.12 (4A)
/Write End Address Low: B7.20 (WCAL), IC11.8 (3Y)
/Write End Address Low ~CS: IC5.13 (~Y2), IC11.9 (3A)
/Write Flags: B8.7 (Latch_Flags), IC12.11 (4Y)
/Write Flags ~CS: IC5.7 (~Y7), IC12.12 (4A)
/Write Interrupt Address High: B2.19 (WCAH), IC12.6 (2Y)
/Write Interrupt Address High ~CS: IC5.10 (~Y5), IC12.4 (2A)
/Write Interrupt Address Low: B2.20 (WCAL), IC12.3 (1Y)
/Write Interrupt Address Low ~CS: IC5.11 (~Y4), IC12.1 (1A)
/Write Start Address High: B1.19 (WSAH), IC11.6 (2Y)
/Write Start Address High ~CS: IC5.14 (~Y1), IC11.4 (2A)
/Write Start Address Low: B1.20 (WSAL), IC11.3 (1Y)
/Write Start Address Low ~CS: IC5.15 (~Y0), IC11.1 (1A)
/~CLK: B8.3 (Set_Interrupt_CLK), IC7.6 (E3), IC8.1 (~MR), IC10.4 (2Y)
/~CPU Address: B3.2 (S), B5.2 (S), IC19.4 (Y)
/~Enable _{OUT}: B8.26 (~E), B9.5 (~EN), J1.19
/~End _{CMP}: B1.5 (~PE), B7.40 (~P=Q)
/~Interrupt _{CMP}: B2.40 (~P=Q), B8.5 (~Set_Interrupt)
/~Interrupt _{OUT}: B8.28 (~INT), J1.18
/~Q3: IC8.7 (CEP), IC10.6 (1Y)
/~RD: IC13.1 (1A), IC13.4 (2A), IC15.3 (A2), IC16.1 (DIR), IC18.16 (B2)
/~RD_{IN}: IC18.4 (A2), J1.13
/~Reset: B8.1 (~Clear_Enable), IC2.1 (~MR), IC18.18 (B0)
/~Reset _{IN}: IC18.2 (A0), J1.1
/~Sound Address: IC3.7 (1Y), IC17.3 (2A)
/~WD: B4.2 (T~DIR), B6.2 (T~DIR), IC11.2 (1B), IC11.5 (2B), IC11.10 (3B), IC11.13 (4B), IC12.2 (1B), IC12.5 (2B), IC12.10 (3B), IC12.13 (4B), IC13.10 (3B), IC13.13 (4B), IC15.2 (A1), IC18.17 (B1)
/~WD_{IN}: IC18.3 (A1), J1.12
/~WR_{A}: B4.23 (L~OE), IC7.14 (~Y1), IC9.9 (3A)
/~WR_{B}: B6.23 (L~OE), IC7.12 (~Y3), IC9.10 (3B)
unnamed: IC1.7 (YA), IC4.2 (A)
unnamed: IC3.2 (1B), IC9.11 (4Y)
